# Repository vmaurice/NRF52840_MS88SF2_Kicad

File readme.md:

# NRF52840 avec le module MS88SF2

Carte schématisée et dessinée avec Kicad.

Cette carte possède le module MS88SF2 de Minew fabriqué avec un microcontrôleur NRF52840. L'objectif ici est d'avoir une carte Bluetooth faible en consommation branchée sur une batterie Lipo. 

Un module lm2902 est aussi présent afin d'amplifier les tensions de sortie des capteurs analogues.

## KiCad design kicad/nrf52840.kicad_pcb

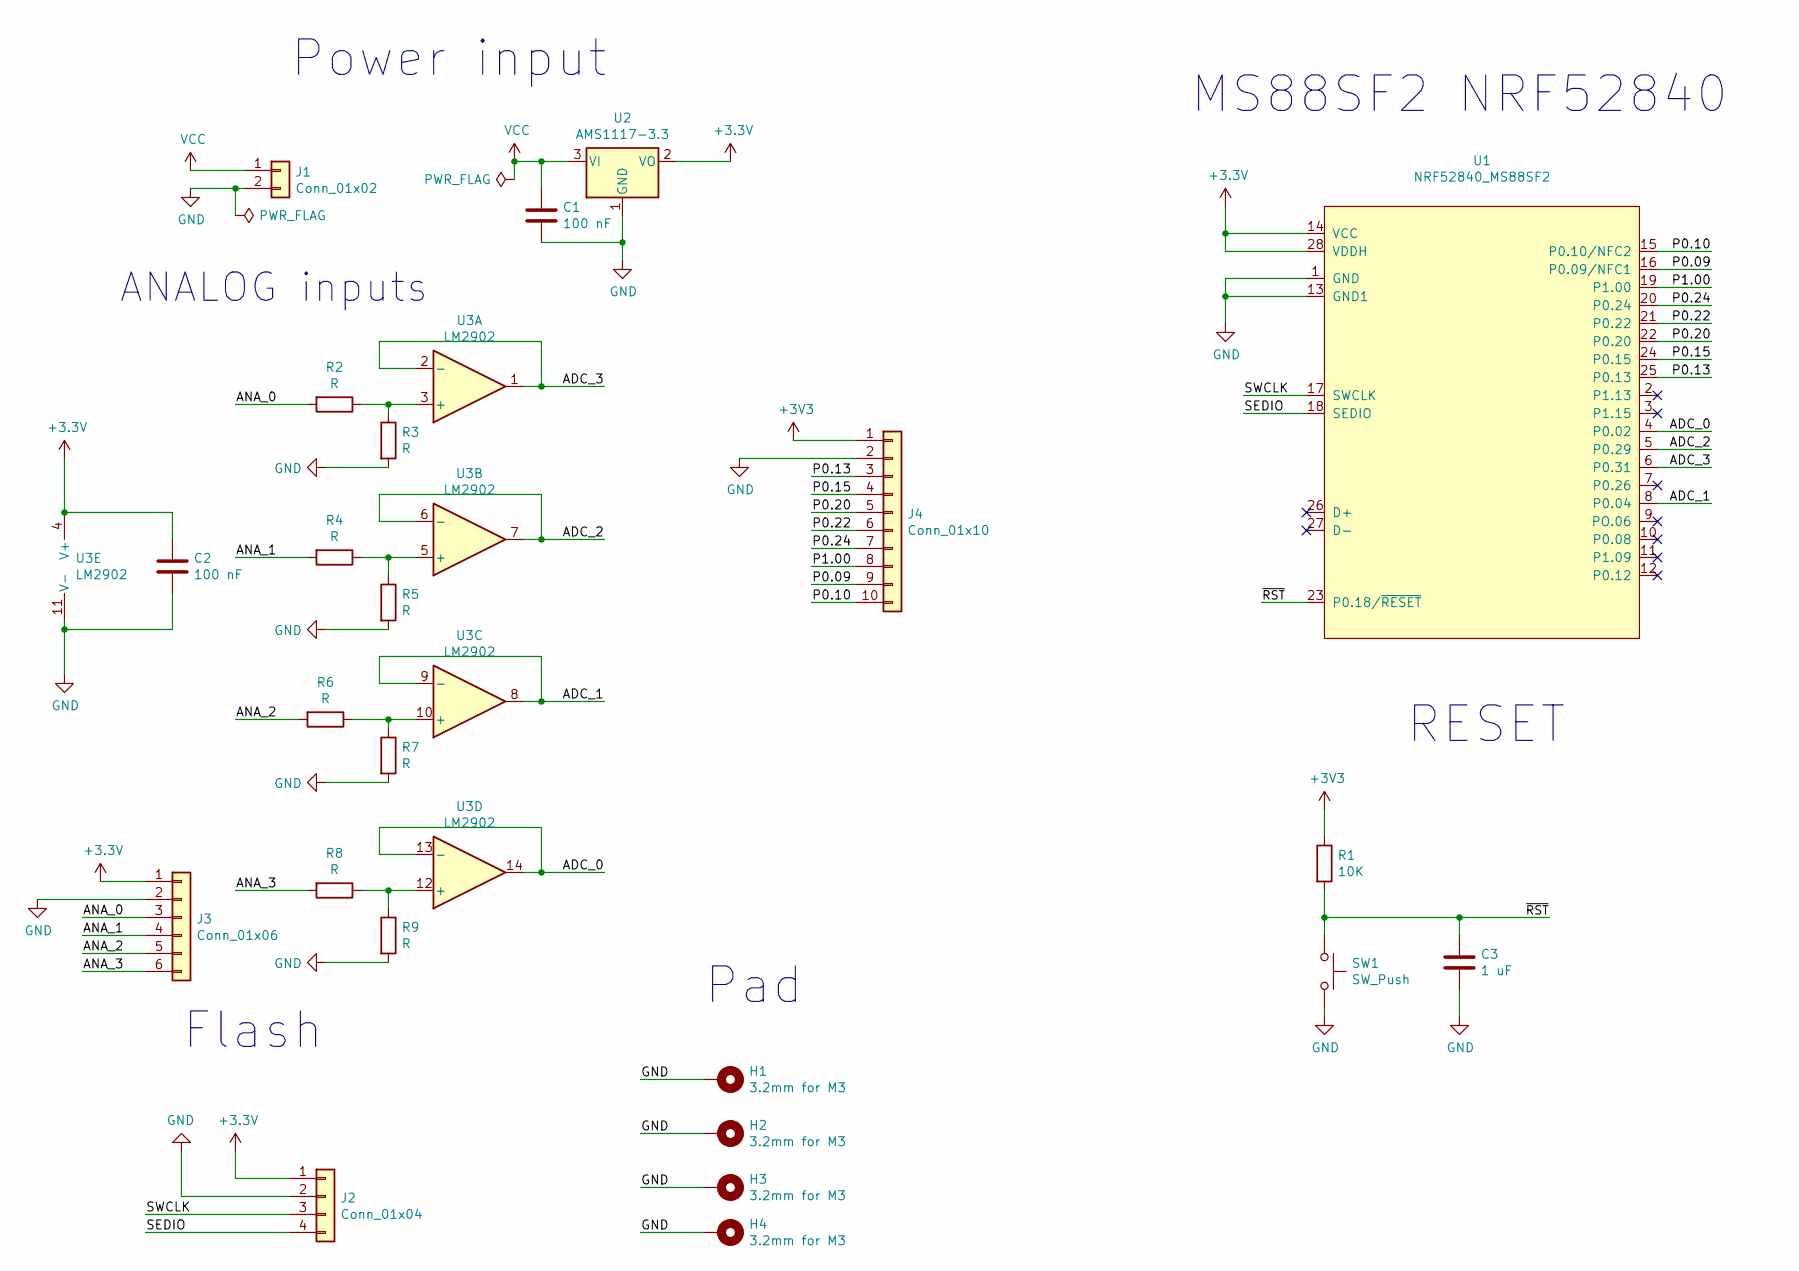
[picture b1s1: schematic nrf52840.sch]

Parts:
C1, C2: 100 nF; C_0805_2012Metric_Pad1.18x1.45mm_HandSolder
C3: 1 uF; C_0805_2012Metric_Pad1.18x1.45mm_HandSolder
H1, H2, H3, H4: 3.2mm for M3; MountingHole_3.2mm_M3_Pad_Via
J1: Conn_01x02; JST_XH_S2B-XH-A_1x02_P2.50mm_Horizontal
J2: Conn_01x04; PinHeader_1x04_P2.54mm_Vertical
J3: Conn_01x06; PinHeader_1x06_P2.54mm_Vertical
J4: Conn_01x10; PinHeader_1x10_P2.54mm_Vertical
R1: 10K; R_0805_2012Metric_Pad1.20x1.40mm_HandSolder
R2, R3, R4, R5, R6, R7, R8, R9: R; C_0805_2012Metric_Pad1.18x1.45mm_HandSolder
SW1: SW_Push; SW_Push_1P1T_NO_CK_KMR2
U1: NRF52840_MS88SF2; MS88SF2
U2: AMS1117-3.3; SOT-223-3_TabPin2
U3: LM2902; SO-14_5.3x10.2mm_P1.27mm

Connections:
/ADC_0: U1.4 (P0.02), U3.13 (-), U3.14
/ADC_1: U1.8 (P0.04), U3.8, U3.9 (-)
/ADC_2: U1.5 (P0.29), U3.6 (-), U3.7
/ADC_3: U1.6 (P0.31), U3.1, U3.2 (-)
/ANA_0: J3.3, R2.2
/ANA_1: J3.4, R4.2
/ANA_2: J3.5, R6.2
/ANA_3: J3.6, R8.2
/P0.09: J4.9, U1.16 (P0.09/NFC1)
/P0.10: J4.10, U1.15 (P0.10/NFC2)
/P0.13: J4.3, U1.25 (P0.13)
/P0.15: J4.4, U1.24 (P0.15)
/P0.20: J4.5, U1.22 (P0.20)
/P0.22: J4.6, U1.21 (P0.22)
/P0.24: J4.7, U1.20 (P0.24)
/P1.00: J4.8, U1.19 (P1.00)
/SEDIO: J2.4, U1.18 (SEDIO)
/SWCLK: J2.3, U1.17 (SWCLK)
/~RST: C3.1, R1.2, SW1.1, U1.23 (P0.18/~RESET)
GND: C1.2, C2.2, C3.2, H1.1, H2.1, H3.1, H4.1, J1.2, J2.2, J3.2, J4.2, R3.2, R5.2, R7.2, R9.2, SW1.2, U1.1 (GND), U1.13 (GND1), U2.1 (GND), U3.11 (V-)
unnamed: R2.1, R3.1, U3.3 (+)
unnamed: R4.1, R5.1, U3.5 (+)
unnamed: R6.1, R7.1, U3.10 (+)
unnamed: R8.1, R9.1, U3.12 (+)
VCC: C1.1, J1.1, U2.3 (VI)

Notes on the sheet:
ANALOG inputs
MS88SF2 NRF52840
Power input
Flash
Pad
RESET

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
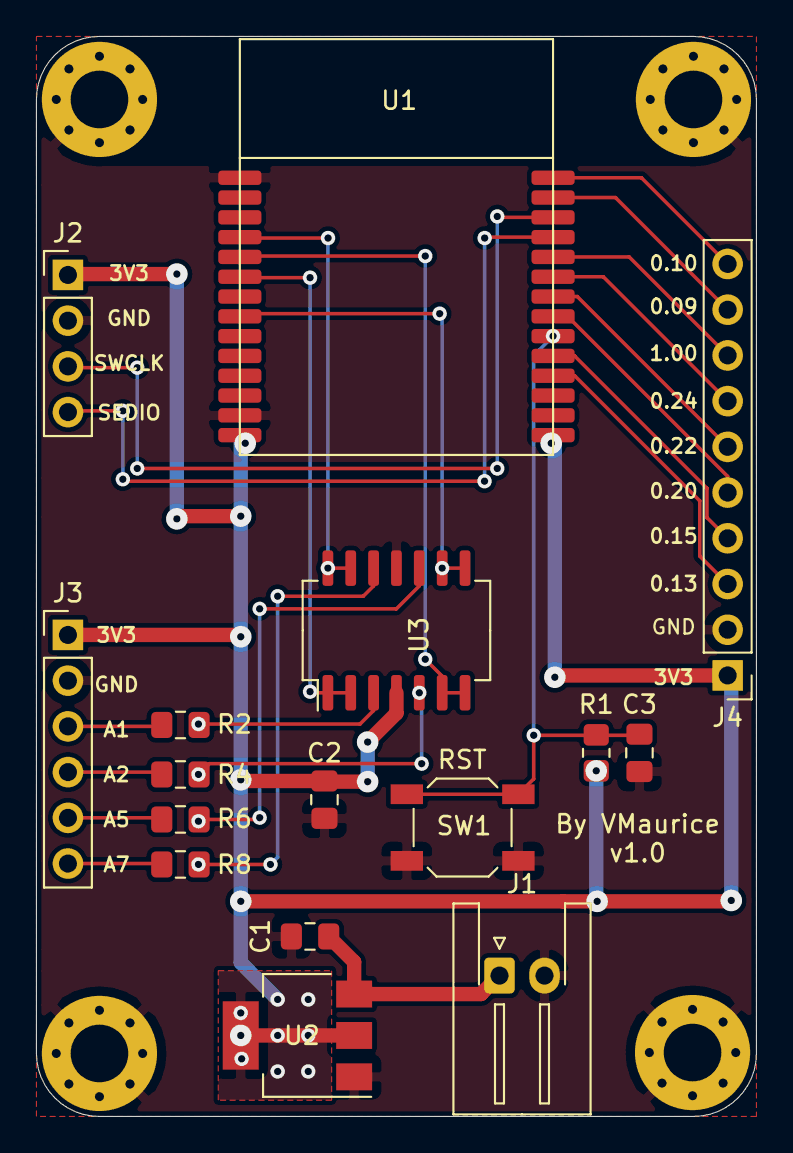
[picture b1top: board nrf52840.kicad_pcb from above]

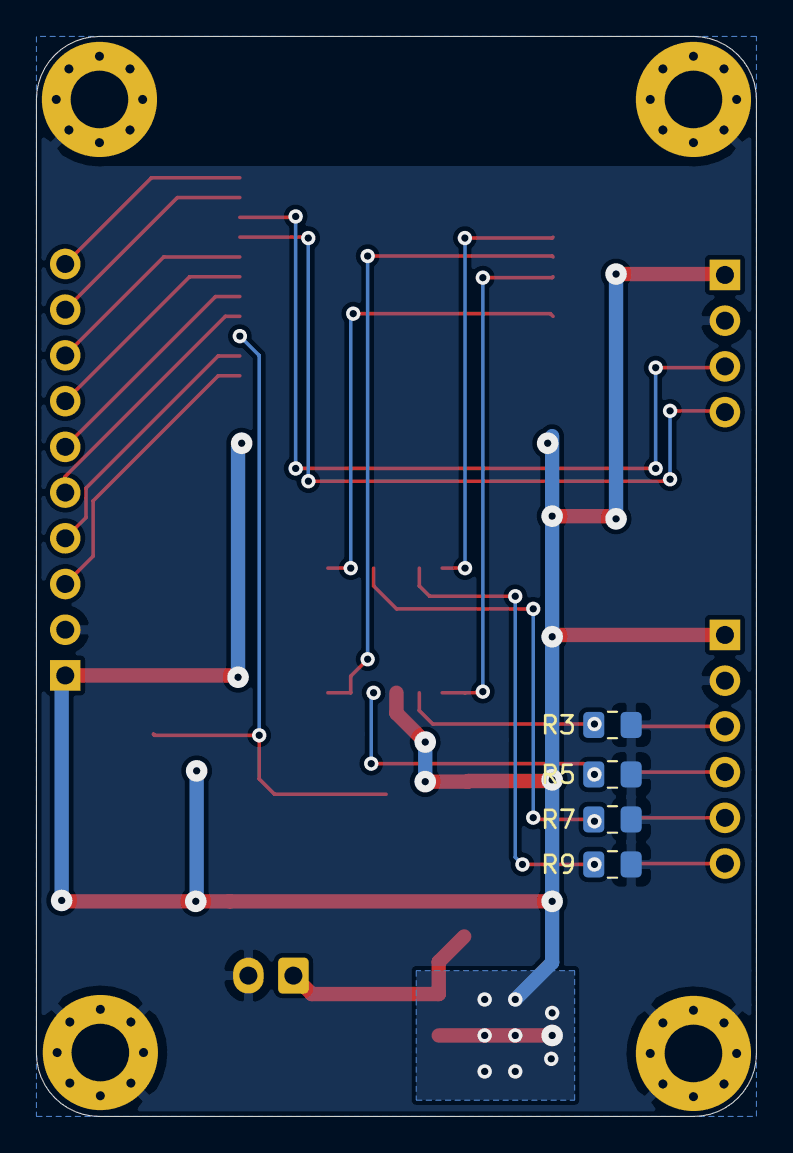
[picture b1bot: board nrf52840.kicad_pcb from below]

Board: 2 copper layers, 40.0 x 60.0 mm, 24 parts (4 on the bottom side), 26 nets.

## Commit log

2021-03-21 version 1
2021-05-05 add resistors for input analogs
